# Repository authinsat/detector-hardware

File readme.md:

#American University ThinSat repository

American University Physics Department
Washington, DC

##Synopsis
This is the support repository for AU's ThinSat project, embarked upon in Spring 2018. Supported by VASpace, Twiggs Space Laboratories, XinaBox, the DC NASA Space Grant Consortium, and the Institute for Integrated Space Science and Technology (ISSTI).

Currently, the only materials housed in this repository are the PCB design files for the particle detector.

Initial PCB design from MIT's Cosmic Watch <https://github.com/spenceraxani/CosmicWatch-Desktop-Muon-Detector-v2>.

This project is licensed under the MIT License; please see license.md for more information.

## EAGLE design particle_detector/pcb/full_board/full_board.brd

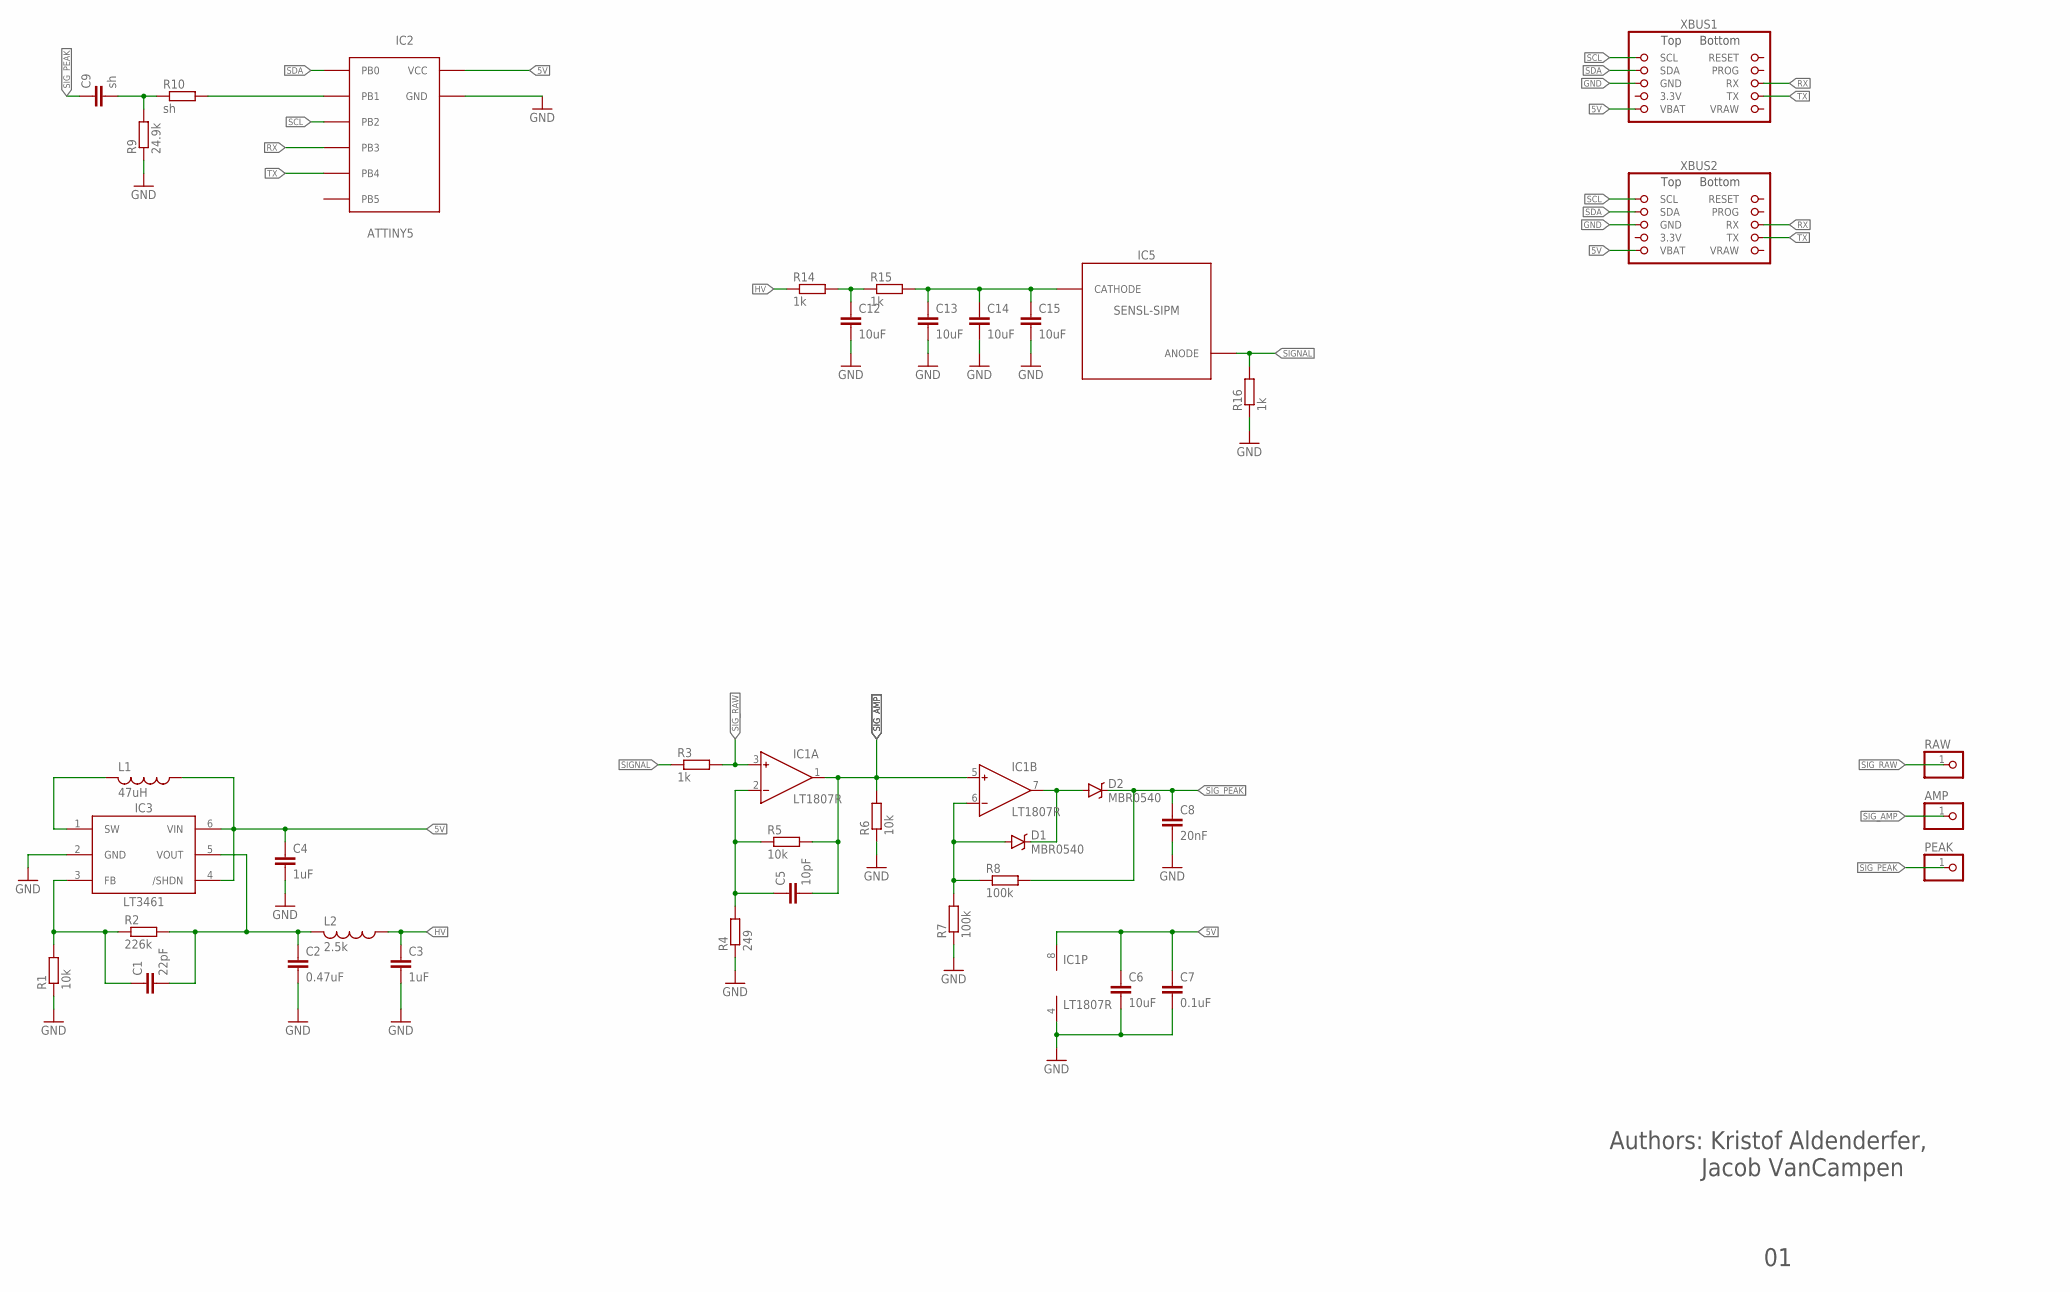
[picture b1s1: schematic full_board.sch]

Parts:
AMP: PINHD-1X1; 1X01
C1: 22pF; C0805K
C2: 0.47uF; C0805K
C3, C4: 1uF; C0805K
C5: 10pF; C0805K
C6, C12, C13, C14, C15: 10uF; C0805K
C7: 0.1uF; C0805K
C8: 20nF; C0805K
C9: sh; C0805K
D1, D2: MBR0540; SMA-DIODE
IC1: LT1807R; SO8
IC2: ATTINY5; PDIP8
IC3: LT3461; SOT23-6
IC5: SENSL-SIPM; MICROFC-60035
L1: 47uH; L3225M
L2: 2.5k; L2012C
PEAK: PINHD-1X1; 1X01
R1, R5, R6: 10k; M0805
R2: 226k; M0805
R3, R14, R15, R16: 1k; M0805
R4: 249; M0805
R7, R8: 100k; M0805
R9: 24.9k; M0805
R10: sh; M0805
RAW: PINHD-1X1; 1X01
XBUS1, XBUS2: XINABOX-XBUS; XBUS_2X05_PAD

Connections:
5V: C4.1, C6.1, C7.1, IC1.8 (V+), IC2.P8 (VCC), IC3.4 (/SHDN), IC3.6 (VIN), L1.1, XBUS1.5 (VBAT), XBUS2.5 (VBAT)
GND: C2.2, C3.2, C4.2, C6.2, C7.2, C8.2, C12.2, C13.2, C14.2, C15.2, IC1.4 (V-), IC2.P4 (GND), IC3.2 (GND), R1.1, R4.1, R6.1, R7.1, R9.1, R16.1, XBUS1.3 (GND), XBUS2.3 (GND)
HV: C3.1, L2.1, R14.1
unnamed: IC3.1 (SW), L1.2
unnamed: D1.C, D2.A, IC1.7 (OUT)
unnamed: C1.1, IC3.3 (FB), R1.2, R2.1
unnamed: D1.A, IC1.6 (IN-), R7.2, R8.1
unnamed: C13.1, C14.1, C15.1, IC5.CATHODE, R15.2
unnamed: C1.2, C2.1, IC3.5 (VOUT), L2.2, R2.2
unnamed: C5.1, IC1.2 (IN-), R4.2, R5.1
unnamed: C9.2, R9.2, R10.1
unnamed: IC2.P6 (PB1), R10.2
unnamed: C12.1, R14.2, R15.1
RX: IC2.P2 (PB3), XBUS1.8 (RX), XBUS2.8 (RX)
SCL: IC2.P7 (PB2), XBUS1.1 (SCL), XBUS2.1 (SCL)
SDA: IC2.P5 (PB0), XBUS1.2 (SDA), XBUS2.2 (SDA)
SIGNAL: IC5.ANODE, R3.1, R16.2
SIG_AMP: AMP.1, C5.2, IC1.1 (OUT), IC1.5 (IN+), R5.2, R6.2
SIG_PEAK: C8.1, C9.1, D2.C, PEAK.1, R8.2
SIG_RAW: IC1.3 (IN+), R3.2, RAW.1
TX: IC2.P3 (PB4), XBUS1.9 (TX), XBUS2.9 (TX)

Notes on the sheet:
Authors: Kristof Aldenderfer, Jacob VanCampen

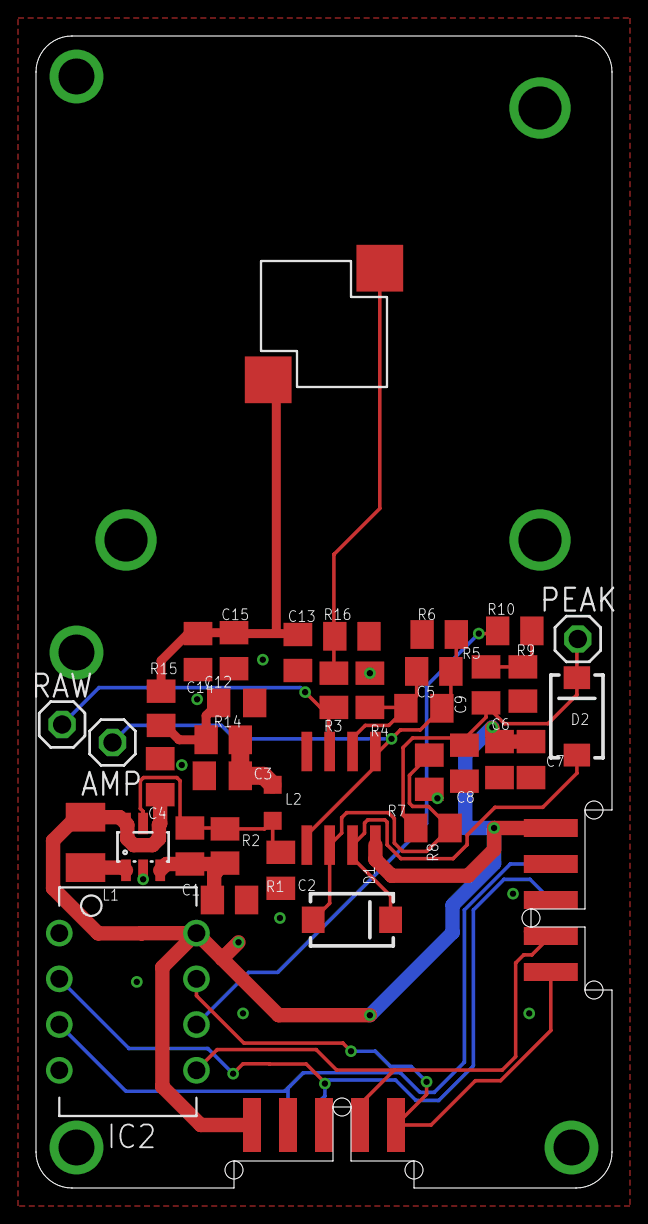
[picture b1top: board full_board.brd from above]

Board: 2 copper layers, 32.0 x 64.0 mm, 39 parts (0 on the bottom side), 21 nets.

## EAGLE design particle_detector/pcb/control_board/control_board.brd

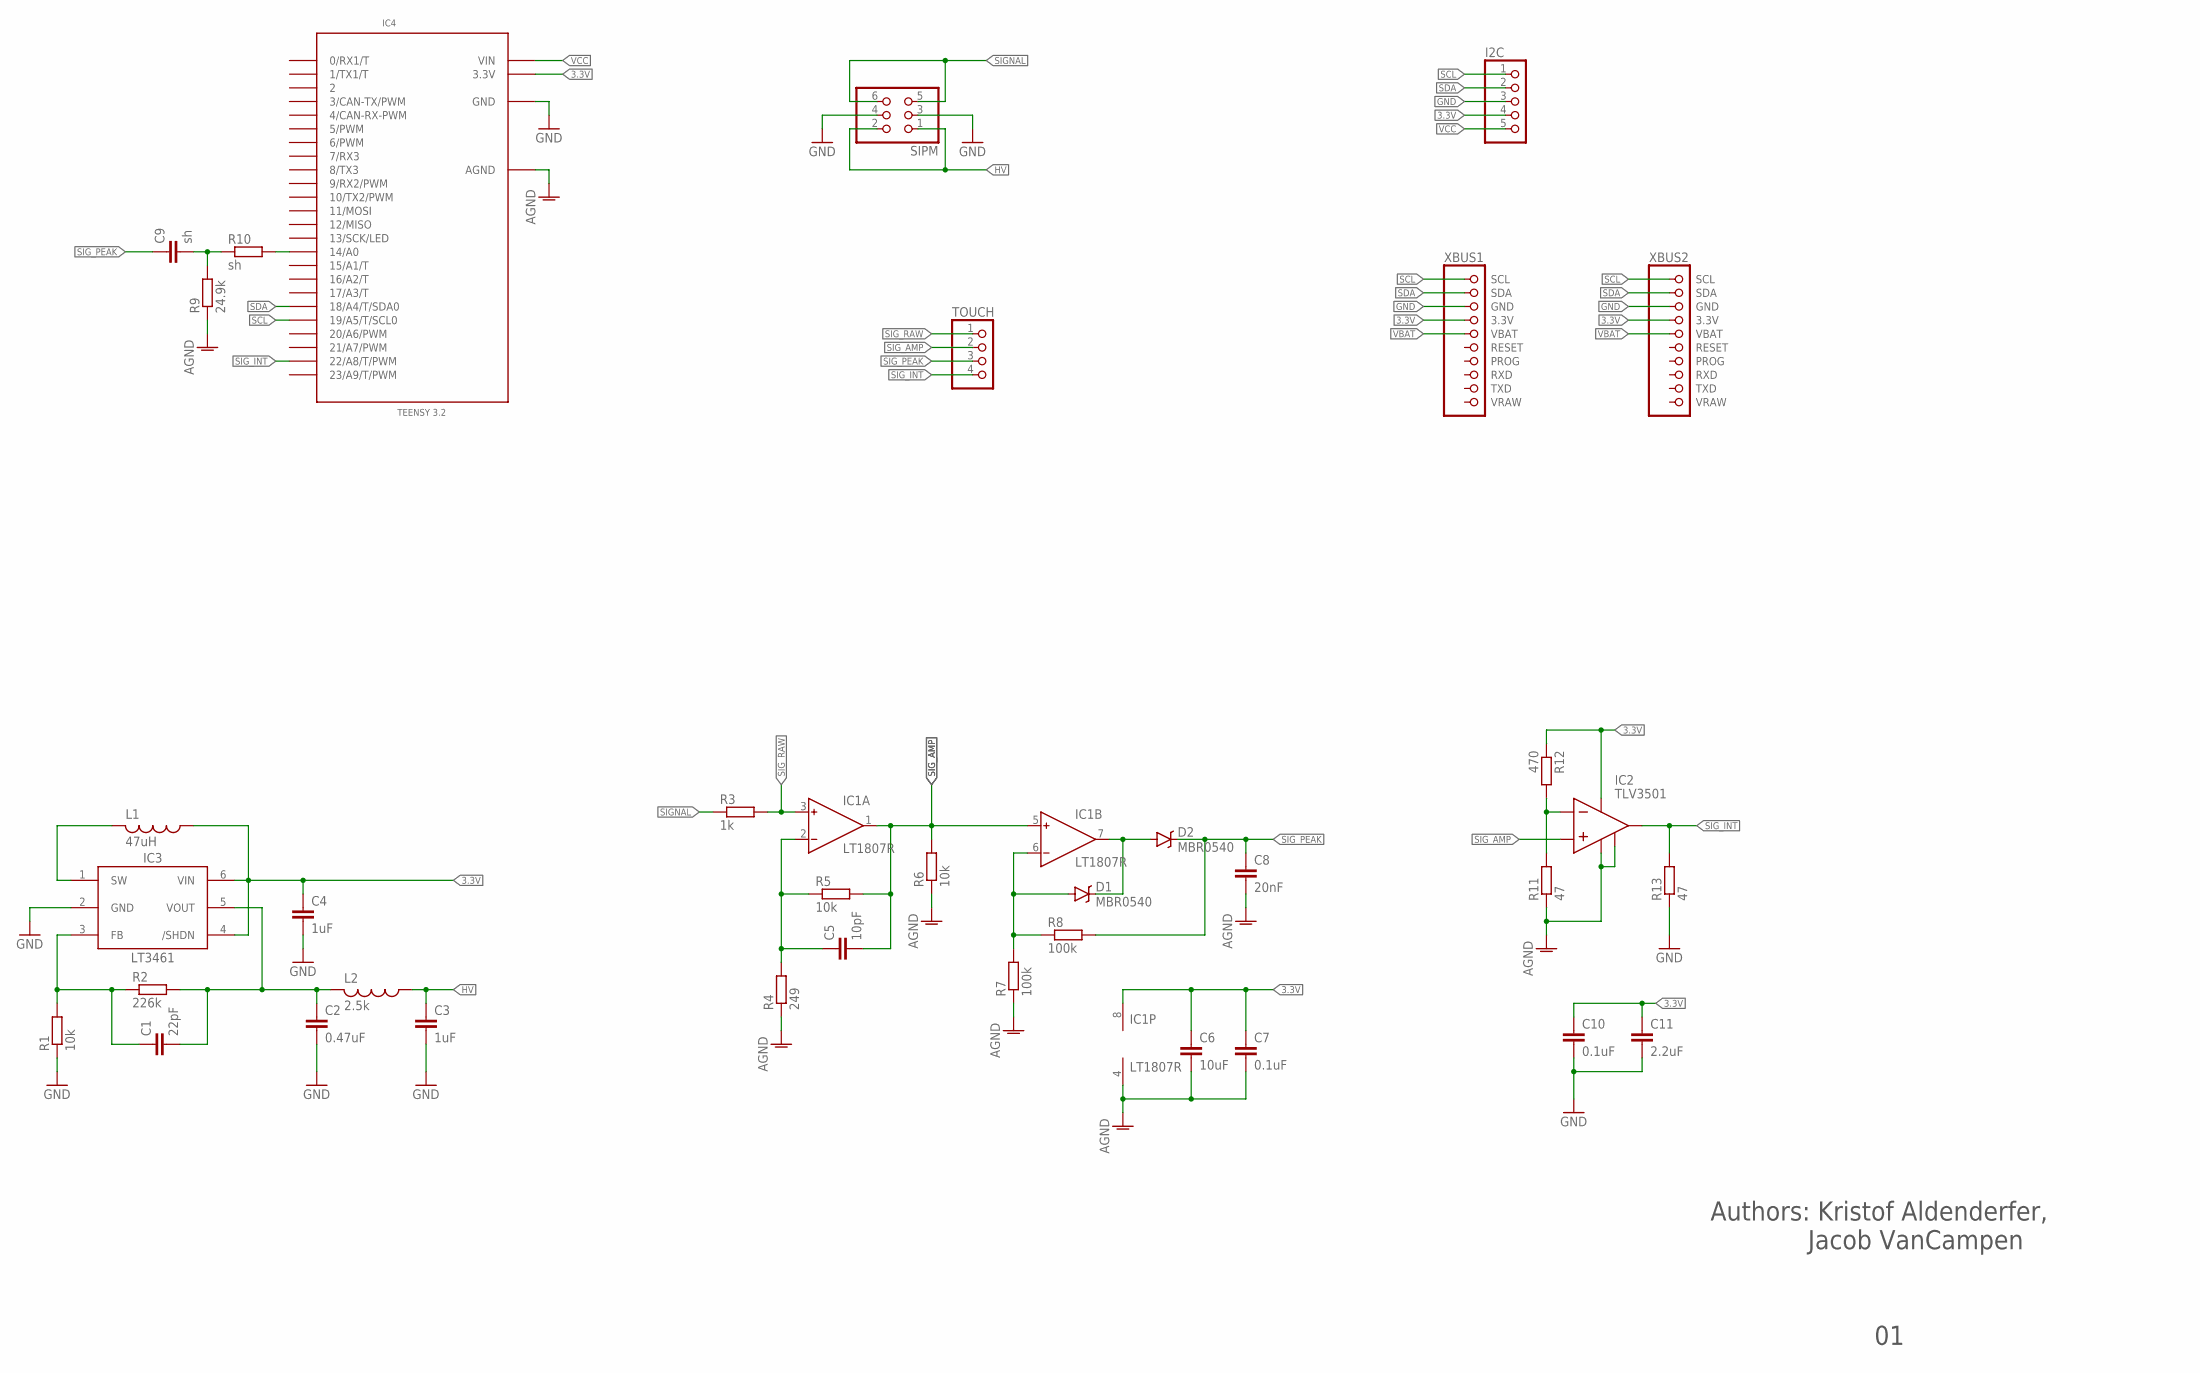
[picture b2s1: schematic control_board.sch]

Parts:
C1: 22pF; C0805K
C2: 0.47uF; C0805K
C3, C4: 1uF; C0805K
C5: 10pF; C0805K
C6: 10uF; C0805K
C7: 0.1uF; C0805K
C8: 20nF; C0805K
C9: sh; C0805K
C10: 0.1uF; C0805
C11: 2.2uF; C0805
D1, D2: MBR0540; SMA-DIODE
I2C: PINHD-1X5; 1X05
IC1: LT1807R; SO8
IC2: TLV3501; SOT23-6
IC3: LT3461; SOT23-6
IC4: TEENSY 3.2; TEENSY_3.2_NO_BOTTOM
L1: 47uH; L3225M
L2: 2.5k; L2012C
R1, R5, R6: 10k; M0805
R2: 226k; M0805
R3: 1k; M0805
R4: 249; M0805
R7, R8: 100k; M0805
R9: 24.9k; M0805
R10: sh; M0805
R11, R13: 47; M0805
R12: 470; M0805
SIPM: PINHD-2X3; 2X03
TOUCH: PINHD-1X4; 1X04
XBUS1, XBUS2: XINABOX-XBUS; XBUS_2X05_PAD

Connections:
3.3V: C4.1, C6.1, C7.1, C10.1, C11.1, I2C.4, IC1.8 (V+), IC2.P$4 (V+), IC3.4 (/SHDN), IC3.6 (VIN), IC4.3.3V, L1.1, R12.1, XBUS1.VCC (3.3V), XBUS2.VCC (3.3V)
AGND: C6.2, C7.2, C8.2, IC1.4 (V-), IC2.P$2 (V-), IC2.P$6 (SHDN), IC4.AGND, R4.1, R6.1, R7.1, R9.1, R11.1
GND: C2.2, C3.2, C4.2, C10.2, C11.2, I2C.3, IC3.2 (GND), IC4.GND, R1.1, R13.1, SIPM.3, SIPM.4, XBUS1.GND, XBUS2.GND
HV: C3.1, L2.1, SIPM.1, SIPM.2
unnamed: IC3.1 (SW), L1.2
unnamed: D1.C, D2.A, IC1.7 (OUT)
unnamed: C1.1, IC3.3 (FB), R1.2, R2.1
unnamed: D1.A, IC1.6 (IN-), R7.2, R8.1
unnamed: IC2.P$1 (IN-), R11.2, R12.2
unnamed: C1.2, C2.1, IC3.5 (VOUT), L2.2, R2.2
unnamed: C5.1, IC1.2 (IN-), R4.2, R5.1
unnamed: C9.2, R9.2, R10.1
unnamed: IC4.14/A0, R10.2
SCL: I2C.1, IC4.19/A5 (19/A5/T/SCL0), XBUS1.SCL, XBUS2.SCL
SDA: I2C.2, IC4.18/A4 (18/A4/T/SDA0), XBUS1.SDA, XBUS2.SDA
SIGNAL: R3.1, SIPM.5, SIPM.6
SIG_AMP: C5.2, IC1.1 (OUT), IC1.5 (IN+), IC2.P$3 (IN+), R5.2, R6.2, TOUCH.2
SIG_INT: IC2.P$5 (OUT), IC4.22/A8 (22/A8/T/PWM), R13.2, TOUCH.4
SIG_PEAK: C8.1, C9.1, D2.C, R8.2, TOUCH.3
SIG_RAW: IC1.3 (IN+), R3.2, TOUCH.1
VBAT: XBUS1.VBAT, XBUS2.VBAT
VCC: I2C.5, IC4.VIN

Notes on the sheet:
Authors: Kristof Aldenderfer, Jacob VanCampen

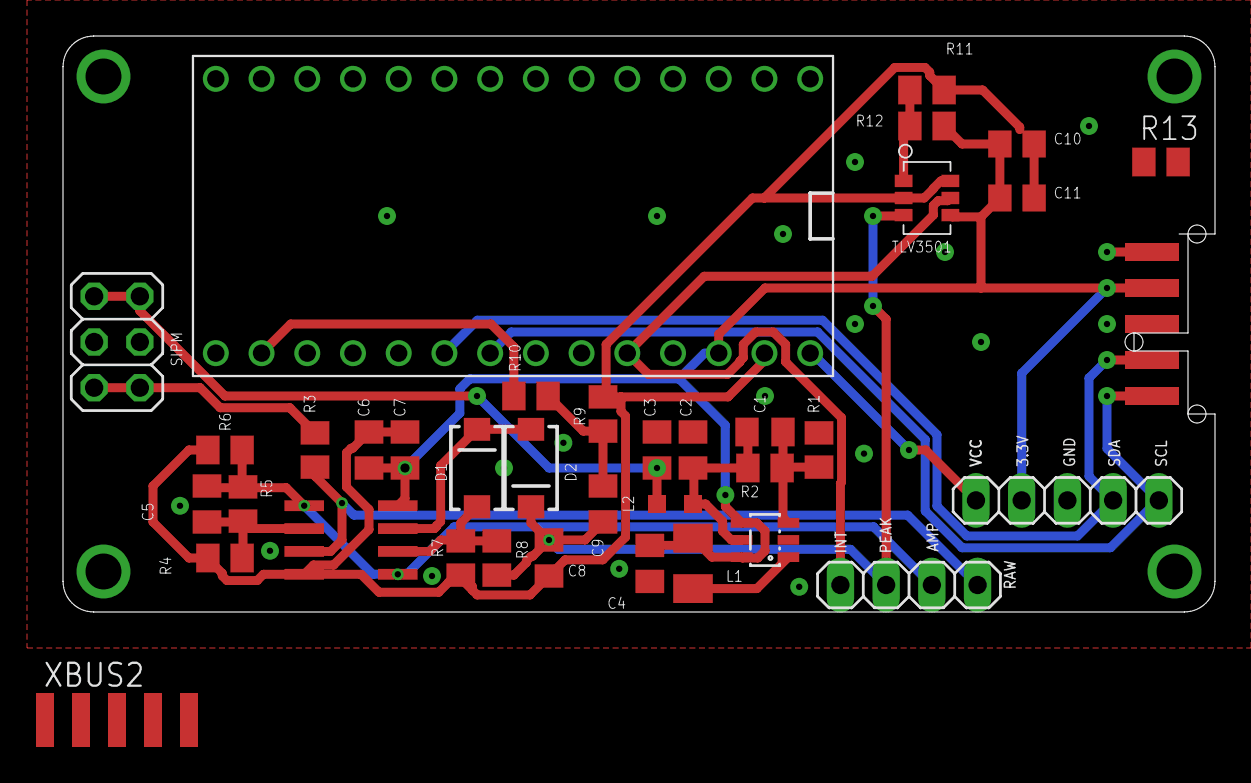
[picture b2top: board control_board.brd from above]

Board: 2 copper layers, 64.0 x 32.0 mm, 37 parts (0 on the bottom side), 22 nets.

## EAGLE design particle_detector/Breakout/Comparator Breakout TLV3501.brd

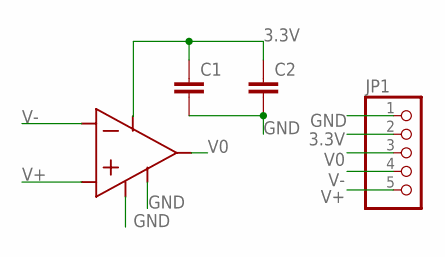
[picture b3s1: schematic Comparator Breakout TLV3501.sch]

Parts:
C1, C2: C-EUC0805; C0805
JP1: PINHD-1X5; 1X05
U$1: TLV3501; SOT23-6

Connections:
3.3V: C1.1, C2.1, JP1.2, U$1.P$4 (V+)
GND: C1.2, C2.2, JP1.1, U$1.P$2 (V-), U$1.P$6 (SHDN)
V0: JP1.3, U$1.P$5 (OUT)
V+: JP1.5, U$1.P$3 (IN+)
V-: JP1.4, U$1.P$1 (IN-)

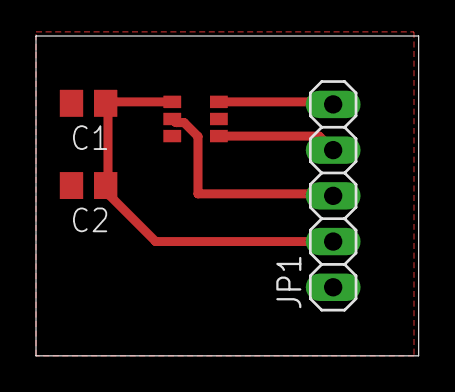
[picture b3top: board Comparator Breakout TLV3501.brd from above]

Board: 2 copper layers, 21.3 x 17.8 mm, 4 parts (0 on the bottom side), 5 nets.

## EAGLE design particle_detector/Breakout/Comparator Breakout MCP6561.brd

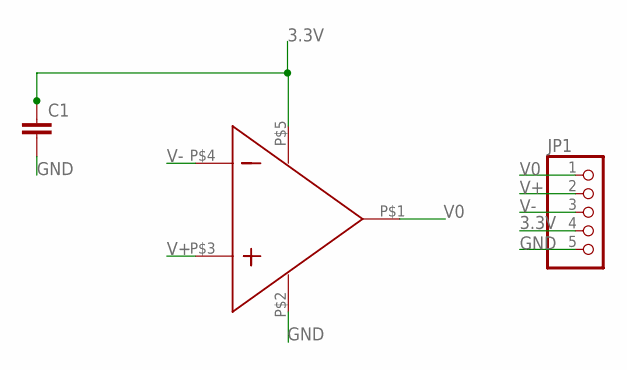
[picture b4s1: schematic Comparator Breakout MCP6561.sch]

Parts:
C1: C-EUC0805; C0805
JP1: PINHD-1X5; 1X05
U$1: MCP6561; SC70-5

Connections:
3.3V: C1.1, JP1.4, U$1.P$5 (VDD)
GND: C1.2, JP1.5, U$1.P$2 (VSS)
V0: JP1.1, U$1.P$1 (OUT)
V+: JP1.2, U$1.P$3 (IN+)
V-: JP1.3, U$1.P$4 (IN-)

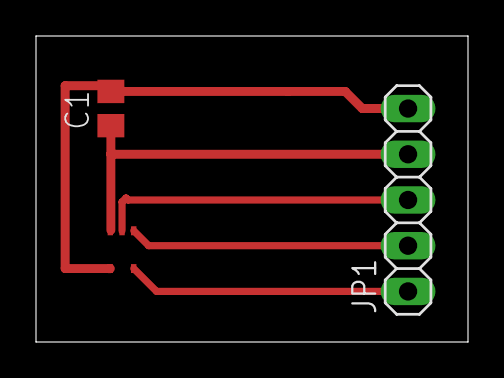
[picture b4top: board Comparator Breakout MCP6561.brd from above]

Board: 2 copper layers, 24.0 x 17.0 mm, 3 parts (0 on the bottom side), 5 nets.

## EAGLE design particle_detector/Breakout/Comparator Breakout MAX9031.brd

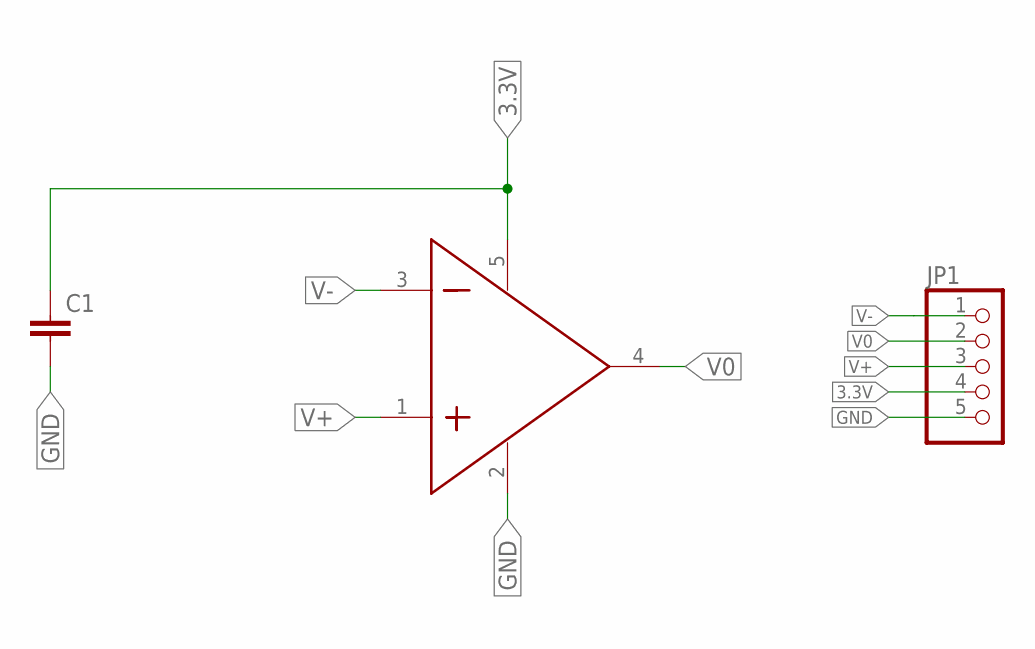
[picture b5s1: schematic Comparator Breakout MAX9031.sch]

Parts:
C1: C-EUC0805; C0805
JP1: PINHD-1X5; 1X05
U$1: MAX9031; SOT23-5

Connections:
3.3V: C1.1, JP1.4, U$1.5 (VDD)
GND: C1.2, JP1.5, U$1.2 (VSS)
V0: JP1.2, U$1.4 (OUT)
V+: JP1.3, U$1.1 (IN+)
V-: JP1.1, U$1.3 (IN-)

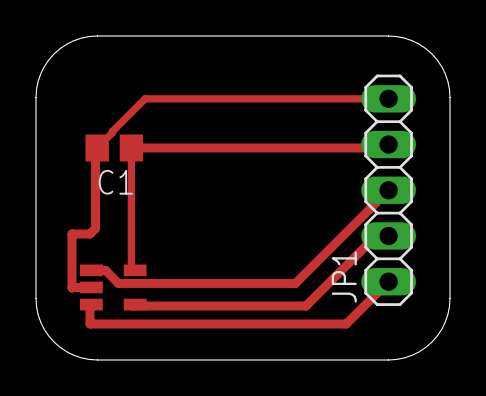
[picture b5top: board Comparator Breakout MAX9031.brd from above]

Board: 2 copper layers, 23.0 x 18.0 mm, 3 parts (0 on the bottom side), 5 nets.

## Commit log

2018-06-19 add start of detector sch
2018-06-21 add gitignore
2018-06-21 complete SiPM and HV schs, partial completion of amplifier, hold schs
2018-06-21 complete first pass of sch
2018-06-22 change EDA name to split boards
2018-06-22 add control board eda
2018-06-26 update EDA with xinabox footprint; board done, awaiting fabhouse confirmation
2018-06-27 clean up traces
2018-07-09 fix AGNd and 3.3V issue; needs DRC
2018-07-20 move to eagle project; fix vcc/3.3v and ind package; remove full board design
2018-08-17 add two breakout board edas
2018-08-20 Fixed Traces on MAX9031
2018-08-20 Fixed the Traces on the MCP6541
2018-10-18 revised boards from a while ago
2018-10-22 Updated footprint with longer pads
2018-11-17 NEW BOARDS HECK YEAH
2018-11-28 Fixed problematic TLVInsect comparator
2018-11-28 booom Jake's private file is going publicgit commit Components/AU_Thinsat_Comparators.lbr -mgit commit Components/AU_Thinsat_Comparators.lbr -m! WHOOOgit commit Components/AU_Thinsat_Comparators.lbr 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
2018-11-29 Stuck the TLV on there, not finished
2018-11-30 ignore zips
2018-11-30 add readme and license
2018-11-30 add lib temp files to gitignore
2018-11-30 reroute traces and fix footprint for TLV chip
2018-11-30 remove VCC traces to DC-DC booster; 3.3V traces remain unrouted
2018-12-02 adjust comparator footprint; route 3.3V traces. send to fab
2019-04-05 not sure if useful, just making sure everything is up-to-date
2019-04-11 begin fix of INT section
2019-04-12 first pass on full board with SiPM integration
2019-04-17 fix traces; this board needs to be flipped to conform to the ICD
2019-05-21 finish full board; still needs Serial connnections (sent to PCBWay 2019.05.19)
2019-05-29 remove empty xbus header, add TX/RX pins to teensy
2019-05-29 swap teensy for new teensy pinout with TX/RX
2019-05-29 layout TX/RX and change power to 5V; send to PCBWay 2019.05.29
2020-02-18 begin conforming to mechanical keepout spec
2020-02-21 final routing for elecrow production, sent 2020.02.21
2020-07-13 Swap the Teensy3.2 for the ATTiny and update nets.
2020-07-20 add MacOS-generated files to ignore
2020-07-20 Change ATTiny pads to save space
2020-08-10 complete a draft of the circuit layout
2020-08-28 Reorganize trace lengths to shorten distances

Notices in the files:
parts and their libraries:
SparkFun-DiscreteSemi: Licensing: Creative Commons ShareAlike 4.0 International - https://creativecommons.org/licenses/by-sa/4.0
